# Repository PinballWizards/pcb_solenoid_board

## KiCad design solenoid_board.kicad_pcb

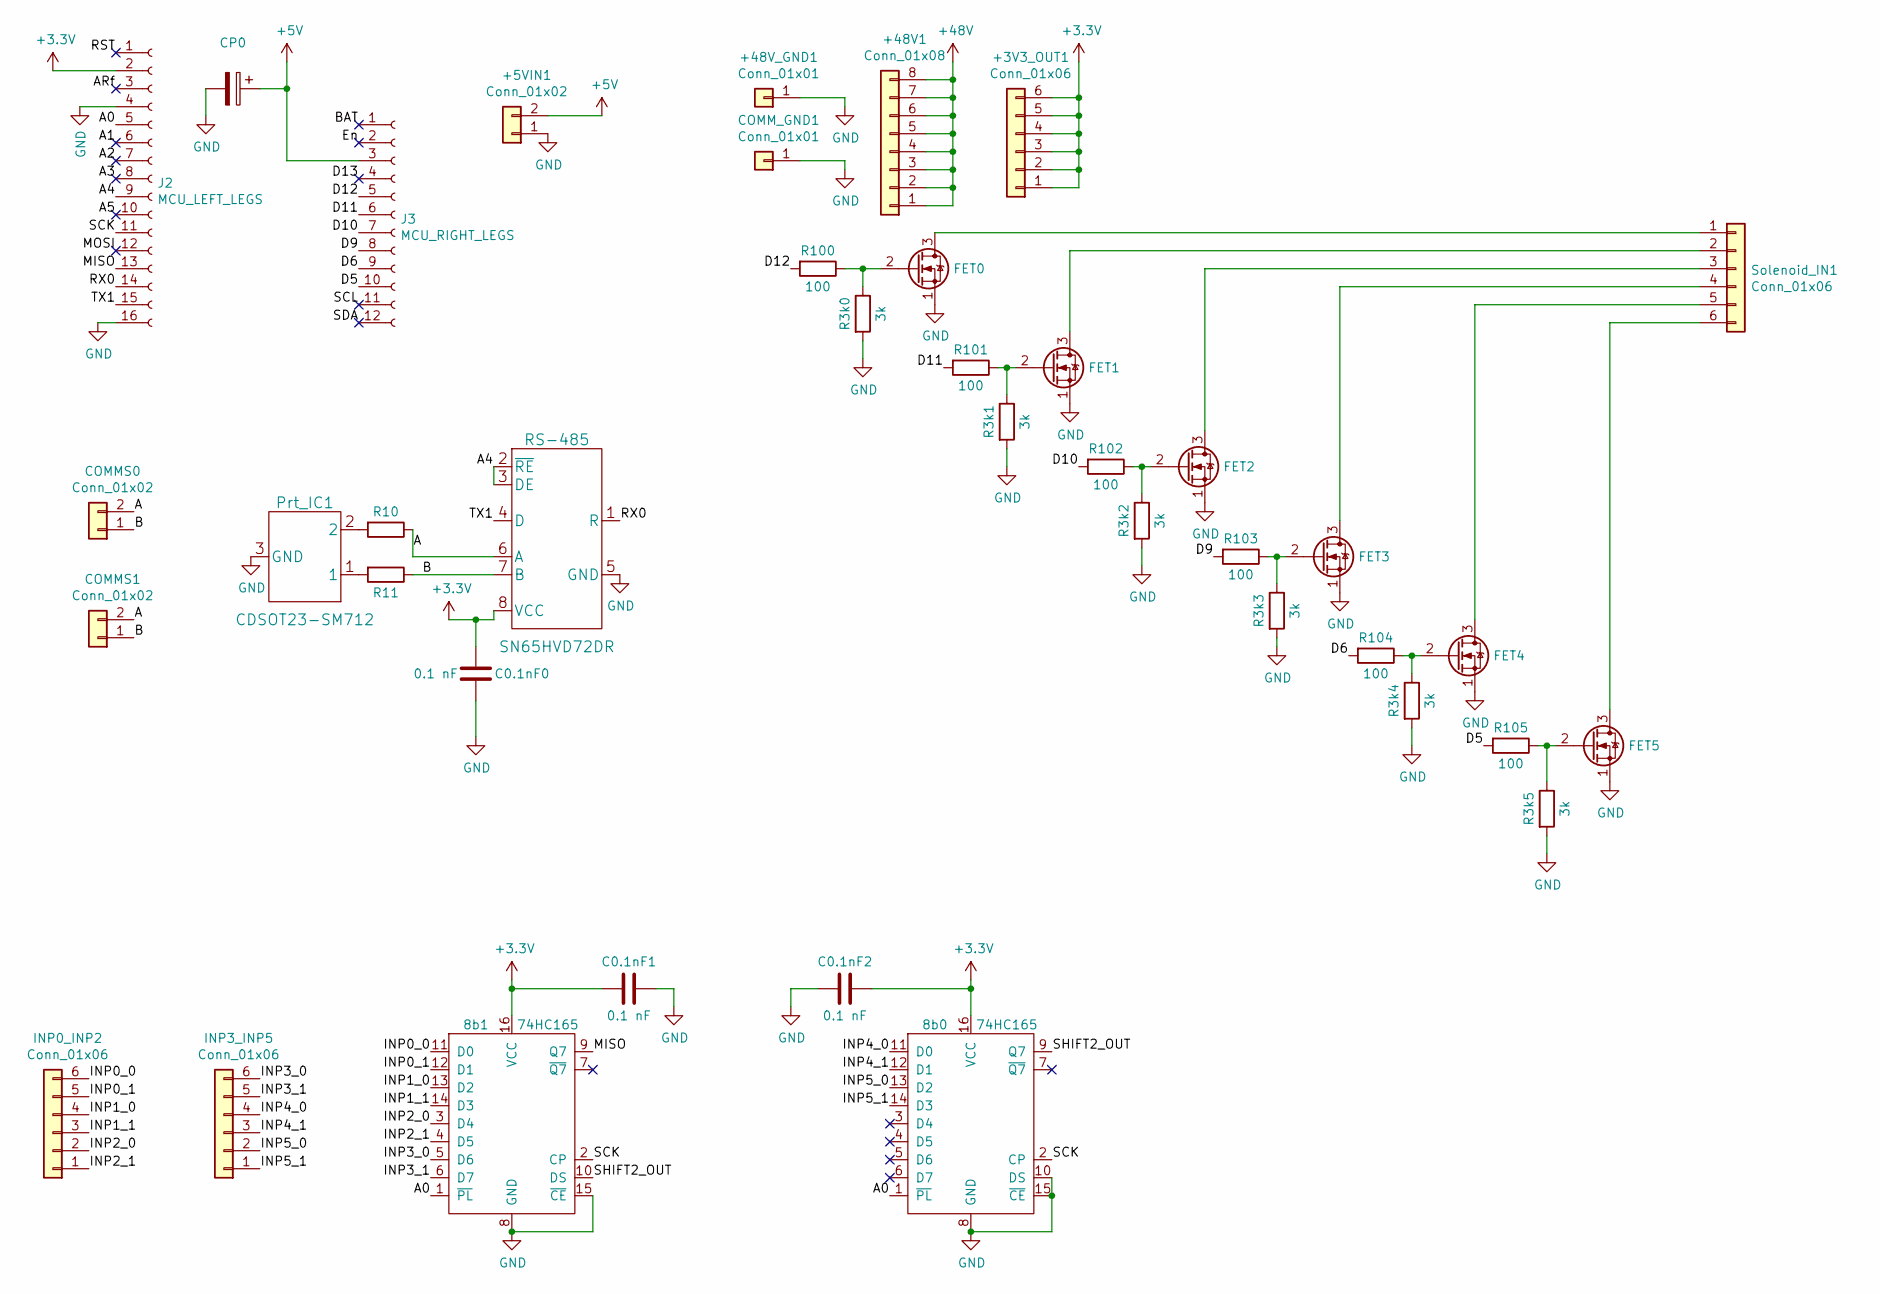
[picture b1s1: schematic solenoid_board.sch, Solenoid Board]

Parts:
8b0, 8b1: 74HC165; SN74HC165DR
+3V3_OUT1: Conn_01x06; PinHeader_1x06_P2.54mm_Vertical
+5VIN1: Conn_01x02; PinHeader_1x02_P2.54mm_Vertical
+48V1: Conn_01x08; PinHeader_1x08_P2.54mm_Vertical
+48V_GND1: Conn_01x01; PinHeader_1x01_P2.54mm_Vertical
C0.1nF0, C0.1nF1, C0.1nF2: 0.1 nF; CP_Radial_D4.0mm_P2.00mm
COMMS0, COMMS1: Conn_01x02; PinHeader_1x02_P2.54mm_Vertical
COMM_GND1: Conn_01x01; PinHeader_1x01_P2.54mm_Vertical
CP0: CP; CP_Radial_D5.0mm_P2.50mm
FET0, FET1, FET2, FET3, FET4, FET5: PHP79NQ08LT; PHP79NQ08LT,127
INP0_INP2, INP3_INP5: Conn_01x06; PinHeader_1x06_P2.54mm_Vertical
J2: MCU_LEFT_LEGS; PinHeader_1x16_P2.54mm_Vertical
J3: MCU_RIGHT_LEGS; PinHeader_1x12_P2.54mm_Vertical
Prt_IC1: CDSOT23-SM712
R3k0, R3k1, R3k2, R3k3, R3k4, R3k5: 3k; R_Axial_DIN0204_L3.6mm_D1.6mm_P5.08mm_Vertical
R10, R11: 10; R_Axial_DIN0204_L3.6mm_D1.6mm_P5.08mm_Vertical
R100, R101, R102, R103, R104, R105: 100; R_Axial_DIN0204_L3.6mm_D1.6mm_P5.08mm_Vertical
RS-485: SN65HVD72DR
Solenoid_IN1: Conn_01x06; PinHeader_1x06_P2.54mm_Vertical

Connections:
+3V3: 8b0.16 (VCC), 8b1.16 (VCC), +3V3_OUT1.1, +3V3_OUT1.2, +3V3_OUT1.3, +3V3_OUT1.4, +3V3_OUT1.5, +3V3_OUT1.6, C0.1nF0.2, C0.1nF1.2, C0.1nF2.1, J2.2, RS-485.8 (VCC)
+5V: +5VIN1.2, CP0.1, J3.3
+48V: +48V1.1, +48V1.2, +48V1.3, +48V1.4, +48V1.5, +48V1.6, +48V1.7, +48V1.8
/A: COMMS0.2, COMMS1.2, R10.1, RS-485.6 (A)
/A0: 8b0.1 (~PL~), 8b1.1 (~PL~), J2.5
/A1: J2.6
/A2: J2.7
/A3: J2.8
/A4: J2.9, RS-485.2 (~RE~), RS-485.3 (DE)
/A5: J2.10
/ARf: J2.3
/B: COMMS0.1, COMMS1.1, R11.1, RS-485.7 (B)
/BAT: J3.1
/D5: J3.10, R105.2
/D6: J3.9, R104.2
/D9: J3.8, R103.2
/D10: J3.7, R102.2
/D11: J3.6, R101.2
/D12: J3.5, R100.2
/D13: J3.4
/En: J3.2
/INP0_0: 8b1.11 (D0), INP0_INP2.6
/INP0_1: 8b1.12 (D1), INP0_INP2.5
/INP1_0: 8b1.13 (D2), INP0_INP2.4
/INP1_1: 8b1.14 (D3), INP0_INP2.3
/INP2_0: 8b1.3 (D4), INP0_INP2.2
/INP2_1: 8b1.4 (D5), INP0_INP2.1
/INP3_0: 8b1.5 (D6), INP3_INP5.6
/INP3_1: 8b1.6 (D7), INP3_INP5.5
/INP4_0: 8b0.11 (D0), INP3_INP5.4
/INP4_1: 8b0.12 (D1), INP3_INP5.3
/INP5_0: 8b0.13 (D2), INP3_INP5.2
/INP5_1: 8b0.14 (D3), INP3_INP5.1
/MISO: 8b1.9 (Q7), J2.13
/MOSI: J2.12
/RST: J2.1
/RX0: J2.14, RS-485.1 (R)
/SCK: 8b0.2 (CP), 8b1.2 (CP), J2.11
/SCL: J3.11
/SDA: J3.12
/SHIFT2_OUT: 8b0.9 (Q7), 8b1.10 (DS)
/TX1: J2.15, RS-485.4 (D)
GND: 8b0.8 (GND), 8b0.10 (DS), 8b0.15 (~CE~), 8b1.8 (GND), 8b1.15 (~CE~), +5VIN1.1, +48V_GND1.1, C0.1nF0.1, C0.1nF1.1, C0.1nF2.2, COMM_GND1.1, CP0.2, FET0.1 (S), FET1.1 (S), FET2.1 (S), FET3.1 (S), FET4.1 (S), FET5.1 (S), J2.4, J2.16, Prt_IC1.3 (GND), R3k0.2, R3k1.2, R3k2.2, R3k3.2, R3k4.2, R3k5.2, RS-485.5 (GND)
unnamed: FET0.2 (G), R3k0.1, R100.1
unnamed: FET0.3 (D), Solenoid_IN1.1
unnamed: FET1.2 (G), R3k1.1, R101.1
unnamed: FET1.3 (D), Solenoid_IN1.2
unnamed: FET2.2 (G), R3k2.1, R102.1
unnamed: FET2.3 (D), Solenoid_IN1.3
unnamed: FET3.2 (G), R3k3.1, R103.1
unnamed: FET3.3 (D), Solenoid_IN1.4
unnamed: FET4.2 (G), R3k4.1, R104.1
unnamed: FET4.3 (D), Solenoid_IN1.5
unnamed: FET5.2 (G), R3k5.1, R105.1
unnamed: FET5.3 (D), Solenoid_IN1.6
unnamed: Prt_IC1.1, R11.2
unnamed: Prt_IC1.2, R10.2

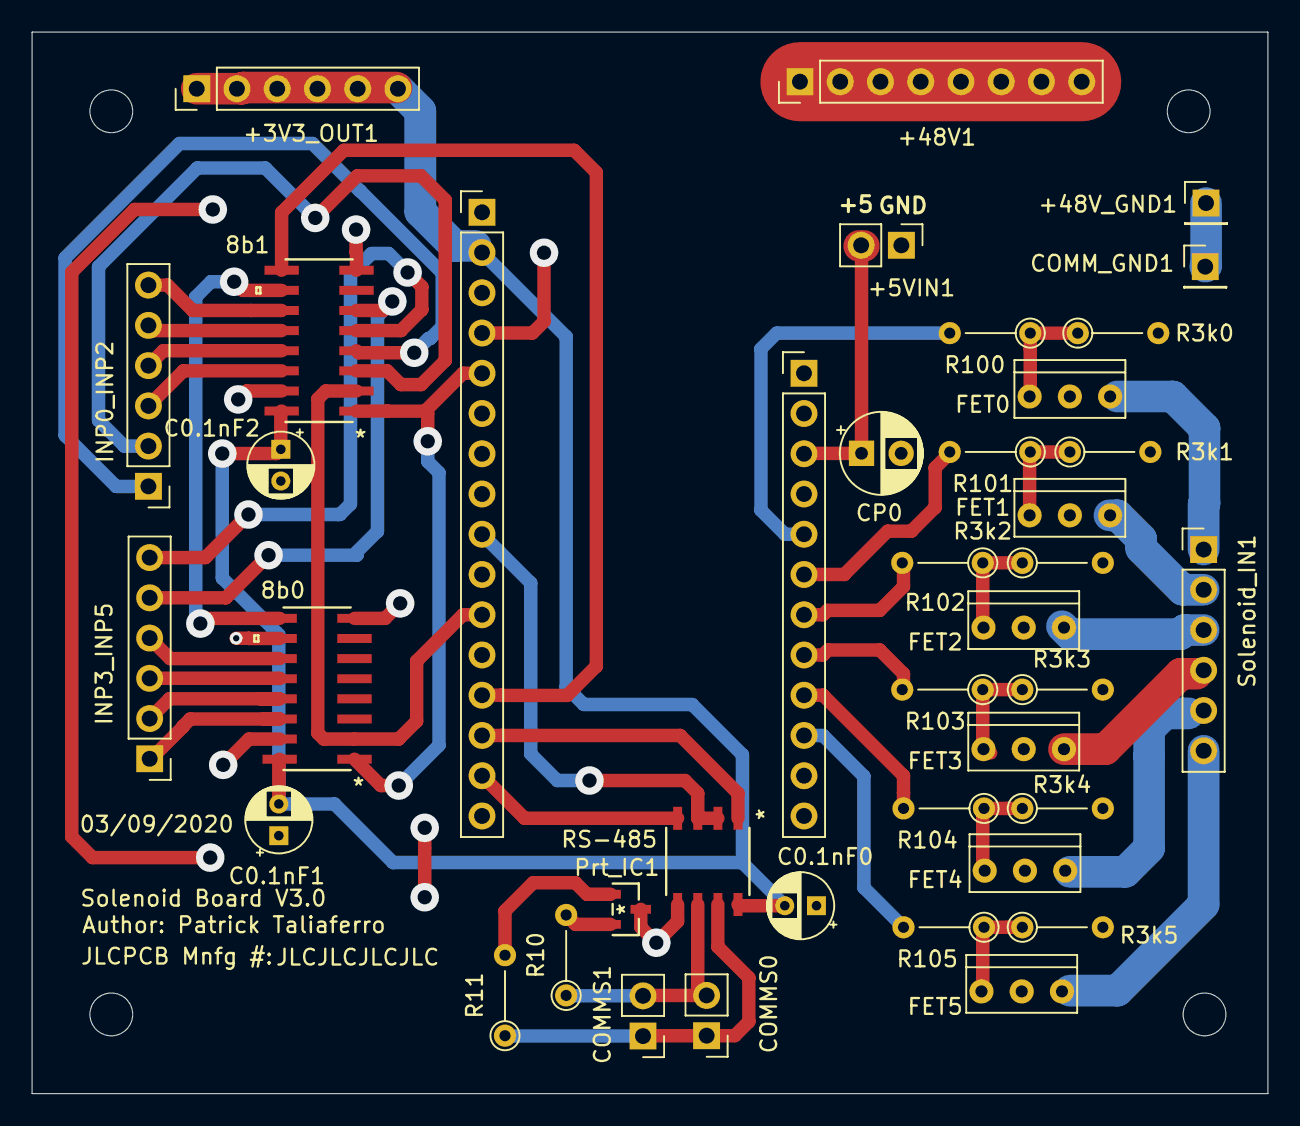
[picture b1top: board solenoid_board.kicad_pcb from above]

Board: 2 copper layers, 78.0 x 67.0 mm, 40 parts (0 on the bottom side), 45 nets.

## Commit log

2020-01-10 Swap to RS485, pre-PCB layout
2020-01-11 COMPLETE ROUTING!!!
2020-01-11 minor tweaks
2020-01-27 update schematic and netlist, fixing traces
2020-01-27 Finish routing
2020-01-27 Add grounding pin
2020-01-30 Stylistic Changes to clean up the Schematic. Added a +5 V screw terminal input to power the MCU. Switched the Shift Registers from +3.3V to +5 V supply, as is typical according to the datasheet. Adde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
2020-01-30 Removed last PWR_FLAG to make schematic cleaner
2020-01-30 Cleaned up Schematic Reference Values - These will be printed on PCB and will make post-production soldering easier. Deleted and remade the layout to start with a clean slate on geometry with the new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
2020-01-30 Reset PCB after design discussion. New plan is to add a 01x06 screw terminal/3v3 rail output, a 01x02 screw terminal for +5V source, a large capacitor on the supply of the MCU, and a small capacitor 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
2020-01-31 Added a +5V Supply input and connected it to the Feather board. Added a second RJ45 port, and connected the 4th and 5th wires of both RJ45 ports together. Added 4 capacitors to maintain a voltage on 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
2020-01-31 Changed the electrolytic capacitor's footprint, deleted all wires in the layout, and rearranged the components.
2020-01-31 Increased board size by half a centimeter on the left side so that the 3.3V terminal strip isn't all up in the feather m0's business. Rearranged the PCB layout geometry a bit. Moved the 8-shift regis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
2020-01-31 Laid about half the wire. Next Step, lay out the wires for the digital electronics
2020-01-31 Wired up the RS-485 Transciever
2020-01-31 Finished one of the 8-bit shifters. Next Steps are to finish routing wire for the second one, and then place a common ground plane on the back.
2020-01-31 Finished second 8-bit shifter and added vias for all the ground pins
2020-01-31 nth draft of routing complete. Common ground laid. Next steps are to add writing to the top of the PCB layout which is elegant and easy to follow.
2020-02-03 Change symbol names and place silk writing onto the board. Next Step: Order PCB
2020-02-03 Clean up labeling on schematic
2020-02-03 Generated Gerber Files. Next Step: Order from JCLPCB.
2020-02-03 Increased thickness for Solenoid signal. High amperage begets a thick wire.
2020-02-03 Started BOM
2020-02-04 Finalized BOM. Next Step: Order enough parts for 5 boards, wait until all the parts and boards come in, assemble and test.
2020-02-05 Added BOM
2020-02-05 Swapped out RJ-45 Connectors in all documents.
2020-02-05 Made Stylistic Changes to Schematic Document, namely making visible the resistor values.
2020-02-05 Found SMD resistors and radial capacitors.
2020-02-06 Deleted all wire connections, changed board geometry, added mounting holes, specified where JLCPCB should print their Mfg. #. Next steps are to draw the new wires after we get V1 shipped in.
2020-02-11 Shaved 10% off the per-board price with new terminal blocks.
2020-02-11 Cut costs by 50% by changing 2-pin terminal block suppliers
2020-02-11 Changed the resistor footprints, and sourced new resistors in the BOM. Need to route the wires.
2020-02-12 Finished V2 Routing.
2020-02-13 Updated .gbr files.
2020-02-13 Added Mounting holes
2020-02-21 Need to: (0) Use thicker traces, (1) Substitute +48V backplane with a wire in the bottom layer, (2) Substitute the screw terminals with pin headers.
2020-02-21 You must change geometry so that the board doesn't catch fire. The +48 Pins will migrate to a rail on the top of the board, next to the +3V3 Rail, and the ground pins will migrate to fill the empty s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
2020-02-21 Changed BOM parts to better reflect the use of pin headers instead of screw terminals.
2020-02-21 Remove .lock file from repo
2020-02-21 De-Routed all wires to allow for the removal of parts.
2020-02-21 Swapped out screw terminals for pin headers.
2020-02-21 Changed Resistor Footprint to save space. Need to rename symbolic connections to allow for better routing.
2020-02-21 Changed pin labels around, re-routed MosFET area, need to route the 8-bit shifter and comms areas.
2020-02-21 Changed Comms area Geometry. Routed wires for Comms.
2020-02-21 V3 Commit. Screw terminals swapped out for pin headers. Geometry changed. The board is now much smaller.
2020-02-21 Changed the BOM
2020-03-09 Debugged Solenoid Footprint issue and 3.3V terminal block issue.
2020-03-09 added pull up resistor.
2020-03-09 Added parts to BOM

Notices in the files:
parts and their libraries:
Copyright 2016 Accelerated Designs. All rights reserved.
